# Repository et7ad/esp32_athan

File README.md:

# Athan clock

> **The website: [et7ad.github.io/esp32_athan](https://et7ad.github.io/esp32_athan/).** Try the clock in your browser
> (its screen, joystick and menu), set one up step by step, listen to every athan and radio station, see your mosque's
> times for the whole year, and build your own with the parts list, the wiring and the case in 3D.

A small Wi-Fi clock that calls the athan at your mosque's prayer times. It shows the time and the next prayer,
plays Quran radio, and can switch a relay before Fajr (one controlling a room light, for example). It runs on an
ESP32-S3 with a small amplifier, and keeps its sounds and a whole year of prayer times in its own memory, so the
athan keeps playing without internet.

> **Have an older clock (ESP8266 with a DFPlayer, "version 2")?** Its firmware and prayer times are in
> [et7ad/esp_athan](https://github.com/et7ad/esp_athan), which supports the clocks already in use. New clocks use
> this repository.

## Why the prayer times come from this repository

Every mosque publishes its prayer times its own way: a PDF, a web page, a spreadsheet, an app. Rather than teach
the clock all of them, this project splits the job of keeping a clock in step with its mosque into two parts.

The clock's part is small, and the same for every mosque. It downloads its mosque's times for a whole year from
this repository on GitHub, as one small file in one fixed format ([prayertimes_specs.md](prayertimes_specs.md)),
and keeps them in its own memory. It never contacts a mosque's website, so a site that changes or goes offline
can't affect it. The list of mosques it offers comes from here as well, so adding a mosque needs no change to the
clock.

The other part, getting each mosque's times right, happens here before anything reaches a clock. A mosque's
timetable becomes that one file in whatever way suits that mosque: a script that reads its PDF or web page, a table
the mosque sends in, or a check against its own source when a time looks wrong. The scripts check every file before
it is published ([guides/maintaining.md](guides/maintaining.md)). Clocks download each new year by themselves; a
correction to the current year reaches a clock when Refresh Prayer Times is pressed on its web page.

That is the main idea of the project: the clock stays simple and keeps working, and all the work of following each
mosque happens in one place, with whatever tools it takes.

## Setting up your clock

> **Wi-Fi: 2.4 GHz only.** The clock can't join a 5 GHz network. If your router shows two networks (for example
> "home" and "home-5G"), pick the one without "5G". A router that uses one name for both bands works too.

1. Plug the clock into a USB-C charger (5 V, 2 A).
2. Connect it to your Wi-Fi. A new clock offers two ways at once; use whichever suits your phone.
   - Option1: Over Bluetooth (easiest), from an Android phone or a computer: open <https://www.improv-wifi.com> in Chrome or Edge (safari won't work as it doesn't support Web Bluetooth). Under "Improv via BLE", the page shows a **Connect** button;
     press **Connect** and pick **athan**. When the clock's screen says **BT: press Select**, push the joystick in.
     Then type your network SSID (which is the name of your Wi-Fi network) and type its password.
   - Option2: With any phone, iPhones included, or a computer: join the Wi-Fi network `AthanFallbackHotspot` with the password `athan404`.
      A setup page opens (if it doesn't, open <http://192.168.4.1>). Pick your network, type its password and save.
3. Choose your mosque. A new clock starts with the Islamic Center of Davis: pick yours by name under **Location**, on the clock's web page (below) or in its menu. The clock then downloads the year's prayer times and its sounds, which takes a few minutes the first time.

From then on the clock runs by itself and keeps its Wi-Fi and settings through power cuts. For the athan it needs
the internet only to set its time after a power cut. If your mosque isn't in the list, open an
[issue](https://github.com/et7ad/esp32_athan/issues) with its timetable. Once it is added here, it shows up on every
clock by itself.

## Using it

### The joystick

The clock has one 5-way joystick: Up, Down, Left, Right, and Select (push it straight in).

| Key | On the clock screen |
|---|---|
| Select | Opens the menu |
| Up | Radio on or off |
| Down | Relay on or off |
| Left, Right | Volume down or up |

While the athan or another sound plays, Up, Down and Select stop it.

In the menu, Up and Down move between rows, Left and Right change the choice, and Select takes it. The last row,
Exit, returns to the clock, and so does a minute without a press.

### The web page

On a phone or computer on the same Wi-Fi, open <http://athan.local>. If it doesn't open (some phones, Android in
particular, can't open `.local` addresses), use the clock's IP address instead: it is on the menu's **Info** row.

The page has everything the menu has, in groups: what plays now, the volumes, the athan on or off for each prayer,
the hourly tick and its hours, the Pre-Fajr Tawashih, the radio and its ten stations, your mosque, the screen, and
updates. A change takes effect at once, and the page always shows what the clock is doing, also after a change
made with the joystick.

The sounds have a page of their own, <http://athan.local/audio> (the **Change Sounds At** link on the main page).
For the athan, the Fajr athan, the tawashih and the hourly tick, choose one from the project's list, listen to a
preview and download it, or upload an MP3 of your own.

### Updates

The clock looks for new firmware when it starts and once a day, and it never installs an update by itself. When a
new version is out, a small up arrow appears at the top right of the screen and stays there until you install it:

Install it with **Firmware** on the web page or the menu's **Update** row, at a time when no prayer is due in the
next few minutes: the clock stands still while it downloads, then restarts with the new version. Your settings,
sounds and prayer times stay.

### Good to know

- When children can reach the clock, lock its buttons with the menu's **Lock Buttons** row. To unlock, switch off
  **Buttons Locked** on the web page, or plug the clock in while holding Up, Down, Left or Right.
- To move the clock to another Wi-Fi network, unplug it, hold Select, and plug it back in. It forgets its network
  and setup starts again.
- Home Assistant finds the clock through its ESPHome integration, with the same controls as the web page. The
  encryption key it asks for is in [guides/using.md](guides/using.md#4-the-web-page) section 4.

The full guide is [guides/using.md](guides/using.md): the screen and its marks, every menu row, your own sounds and
radio stations, and what to do if your router keeps dropping the clock.

## What it does

- Calls the athan at Dhuhr, Asr, Maghrib and Isha, and a separate Fajr athan at Fajr, each at its own volume. Each
  prayer's athan can be switched off on its own.
- Downloads a whole year of your mosque's prayer times from this repository and keeps it. Once the clock is set,
  the athan needs no internet.
- Plays Quran radio from ten slots. They follow this project's station list, and any slot can play a link of your
  own instead.
- Pre-Fajr Tawashih (off by default): 25 minutes before Fajr it switches the relay on and plays a tawashih, then
  switches the relay off 15 minutes after it ends.
- Plays an hourly tick during the hours you choose.
- Lets you choose each sound (athan, Fajr athan, tawashih, tick) from the project's list, or upload your own.
- Is set up from a phone, over Bluetooth or through its own Wi-Fi hotspot.
- Has a web page, works with Home Assistant, and updates its own firmware.
- Comes with a one-colour OLED or a colour screen, and keeps calling the athan even if the screen fails.

## Guides

| You want to | Read |
|---|---|
| Set up a clock and use it | [guides/using.md](guides/using.md) |
| Build one | [guides/building.md](guides/building.md) |
| Keep the prayer times, sounds and stations up to date, or publish firmware | [guides/maintaining.md](guides/maintaining.md) |
| Understand or change the firmware | [DEVELOPER.md](DEVELOPER.md), and [firmware_rules.md](firmware_rules.md) for the rules it depends on |
| Understand the circuit board | [HARDWARE.md](HARDWARE.md), [max98357a_amplifier.md](max98357a_amplifier.md), [microcontroller_demand.md](microcontroller_demand.md) |
| Read or write a prayer-time file | [prayertimes_specs.md](prayertimes_specs.md) |

**Status:** firmware 3.0.0 runs on the breadboard prototype. The circuit board (`hardware/pcb/`) and its
3D-printed case (`hardware/enclosure/`) are designed.

## Repository layout

```text
firmware/
  athan.yaml               everything the clock does (ESPHome)
  displays/                one file per display (oled.yaml, tft.yaml); athan.yaml uses one of them
  partitions.csv           the 16 MB flash layout (two app slots, prayer years, sounds)
  web_audio_link.js        makes the web page's Change Sounds At value a link
  components/athan/        the custom component: stored sounds, lists, radio, prayer years, the sounds page
  sounds/                  click.wav and volume.wav, the two menu tones
  tests/                   tests and checks that run on a computer
docs/                      everything the clocks download, and the website (GitHub Pages)
  athantimes/              mosques.json (the mosques) and a folder per mosque, a file per year
  audio/                   catalog.json and the sounds (athan/ fajr/ tawashih/ tick/)
  radio/stations.json      the project's ten radio stations
  *.html, assets/          the website's pages, scripts, pictures and 3D models
guides/                    using.md, building.md, maintaining.md
scripts/                   prayer-time converters, the sound library builder, the release manifest
hardware/pcb/              the KiCad project
hardware/enclosure/        the 3D-printed case (STL to print, STEP, the CadQuery script)
hardware/programmer/       a press-in programmer for J6 (KiCad project)
images/                    pictures for the guides
build_firmware.sh          build, flash and update without Docker (guides/building.md)
flash_firmware.sh          flash existing files over Wi-Fi or USB, without building
README.md  HARDWARE.md  DEVELOPER.md  firmware_rules.md  prayertimes_specs.md
max98357a_amplifier.md  microcontroller_demand.md
```

## License

See [LICENSE](LICENSE).

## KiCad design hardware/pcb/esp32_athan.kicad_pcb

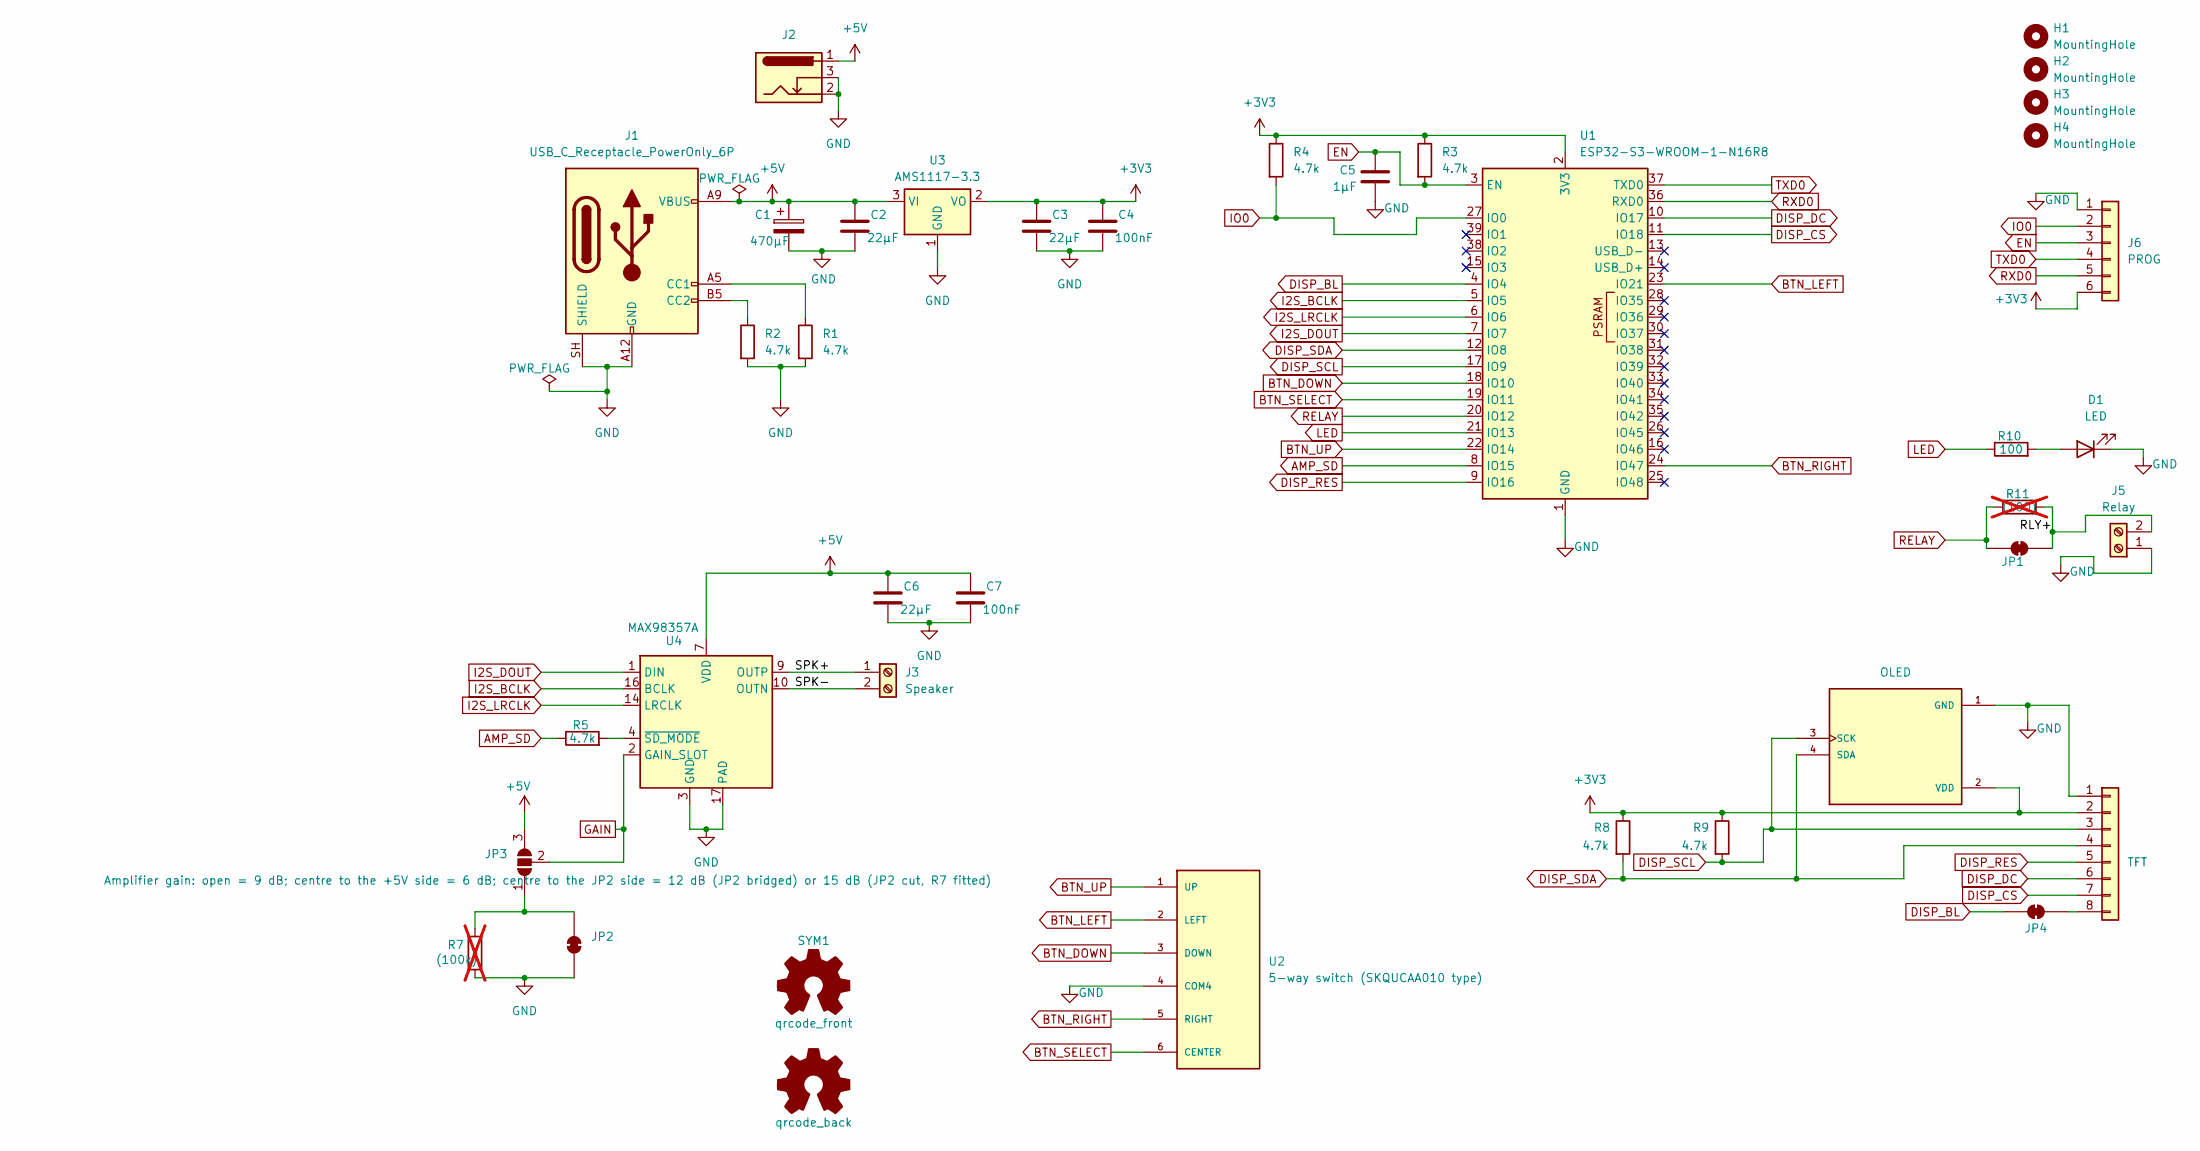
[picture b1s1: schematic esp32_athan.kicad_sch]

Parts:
C1: 470µF; CP_Elec_8x10.5; LCSC C178530
C2, C3, C6: 22µF; C_1206_3216Metric; LCSC C12891
C4, C7: 100nF; C_1206_3216Metric; LCSC C24497
C5: 1µF; C_1206_3216Metric; LCSC C1848
D1: LED; LED_1206_3216Metric_Pad1.42x1.75mm_HandSolder; LCSC C130717
DS1: OLED; LCD_OLED_128X64_1.3_I2C; PARTREV NA
DS2: TFT; Display_TFT_1.54in_ST7789_240x240_8pin
H1, H2, H3, H4: MountingHole; MountingHole_3.2mm_M3
J1: USB_C_Receptacle_PowerOnly_6P; USB_C_Receptacle_GCT_USB4125_6P_BothSides; LCSC C3151650
J2: Barrel_Jack; BarrelJack_CUI_PJ-102AH_Horizontal; LCSC C3096093
J3: Speaker; TerminalBlock_MaiXu_MX126-5.0-02P_1x02_P5.00mm; LCSC C5188434
J5: Relay; TerminalBlock_MaiXu_MX126-5.0-02P_1x02_P5.00mm; LCSC C5188434
J6: PROG; PinHeader_1x06_P2.54mm_Vertical
JP1, JP2, JP4: SolderJumper_2_Bridged; SolderJumper-2_P1.3mm_Bridged_RoundedPad1.0x1.5mm
JP3: SolderJumper_3_Open; SolderJumper-3_P1.3mm_Open_RoundedPad1.0x1.5mm
R1, R2, R3, R4, R5, R8, R9: 4.7k; R_1206_3216Metric; LCSC C17936
R7: (100k); R_1206_3216Metric; LCSC C17900; not fitted
R10: 100; R_1206_3216Metric; LCSC C17901
R11: (100); R_1206_3216Metric; LCSC C17901; not fitted
SYM1: qrcode_front; QRCode_esp32_athan_p3
SYM2: qrcode_back; QRCode_esp32_athan_p3
U1: ESP32-S3-WROOM-1-N16R8; ESP32-S3-WROOM-1; LCSC C2913202
U2: 5-way switch (SKQUCAA010 type); SKQUAAA010
U3: AMS1117-3.3; SOT-223-3_TabPin2; LCSC C6186
U4: MAX98357A; TQFN-16-1EP_3x3mm_P0.5mm_EP1.23x1.23mm; LCSC C910544

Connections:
+3V3: C3.1, C4.1, DS1.2 (VDD), DS2.2, J6.6, R3.1, R4.1, R8.1, R9.1, U1.2 (3V3), U3.2 (VO)
+5V: C1.1, C2.1, C6.1, C7.1, J1.A9 (VBUS), J1.B9 (VBUS), J2.1, JP3.3 (B), U3.3 (VI), U4.7 (VDD), U4.8 (VDD)
/RLY+: J5.2, JP1.2 (B), R11.2
/SPK+: J3.1, U4.9 (OUTP)
/SPK-: J3.2, U4.10 (OUTN)
AMP_SD: R5.1, U1.8 (IO15)
BTN_DOWN: U1.18 (IO10), U2.3 (DOWN)
BTN_LEFT: U1.23 (IO21), U2.2 (LEFT)
BTN_RIGHT: U1.24 (IO47), U2.5 (RIGHT)
BTN_SELECT: U1.19 (IO11), U2.6 (CENTER)
BTN_UP: U1.22 (IO14), U2.1 (UP)
DISP_BL: JP4.1 (A), U1.4 (IO4)
DISP_CS: DS2.7, U1.11 (IO18)
DISP_DC: DS2.6, U1.10 (IO17)
DISP_RES: DS2.5, U1.9 (IO16)
DISP_SCL: DS1.3 (SCK), DS2.3, R9.2, U1.17 (IO9)
DISP_SDA: DS1.4 (SDA), DS2.4, R8.2, U1.12 (IO8)
EN: C5.1, J6.3, R3.2, U1.3 (EN)
GAIN: JP3.2 (C), U4.2 (GAIN_SLOT)
GND: C1.2, C2.2, C3.2, C4.2, C5.2, C6.2, C7.2, D1.1 (K), DS1.1 (GND), DS2.1, J1.A12 (GND), J1.B12 (GND), J1.SH (SHIELD), J2.2, J2.3, J5.1, J6.1, JP2.1 (A), R1.2, R2.2, R7.2, U1.1 (GND), U1.40 (GND), U1.41 (GND), U2.4 (COM4), U3.1 (GND), U4.3 (GND), U4.11 (GND), U4.15 (GND), U4.17 (PAD)
I2S_BCLK: U1.5 (IO5), U4.16 (BCLK)
I2S_DOUT: U1.7 (IO7), U4.1 (DIN)
I2S_LRCLK: U1.6 (IO6), U4.14 (LRCLK)
IO0: J6.2, R4.2, U1.27 (IO0)
LED: R10.1, U1.21 (IO13)
unnamed: D1.2 (A), R10.2
unnamed: DS2.8, JP4.2 (B)
unnamed: J1.A5 (CC1), R1.1
unnamed: J1.B5 (CC2), R2.1
unnamed: JP2.2 (B), JP3.1 (A), R7.1
unnamed: R5.2, U4.4 (~SD_MODE)
RELAY: JP1.1 (A), R11.1, U1.20 (IO12)
RXD0: J6.5, U1.36 (RXD0)
TXD0: J6.4, U1.37 (TXD0)

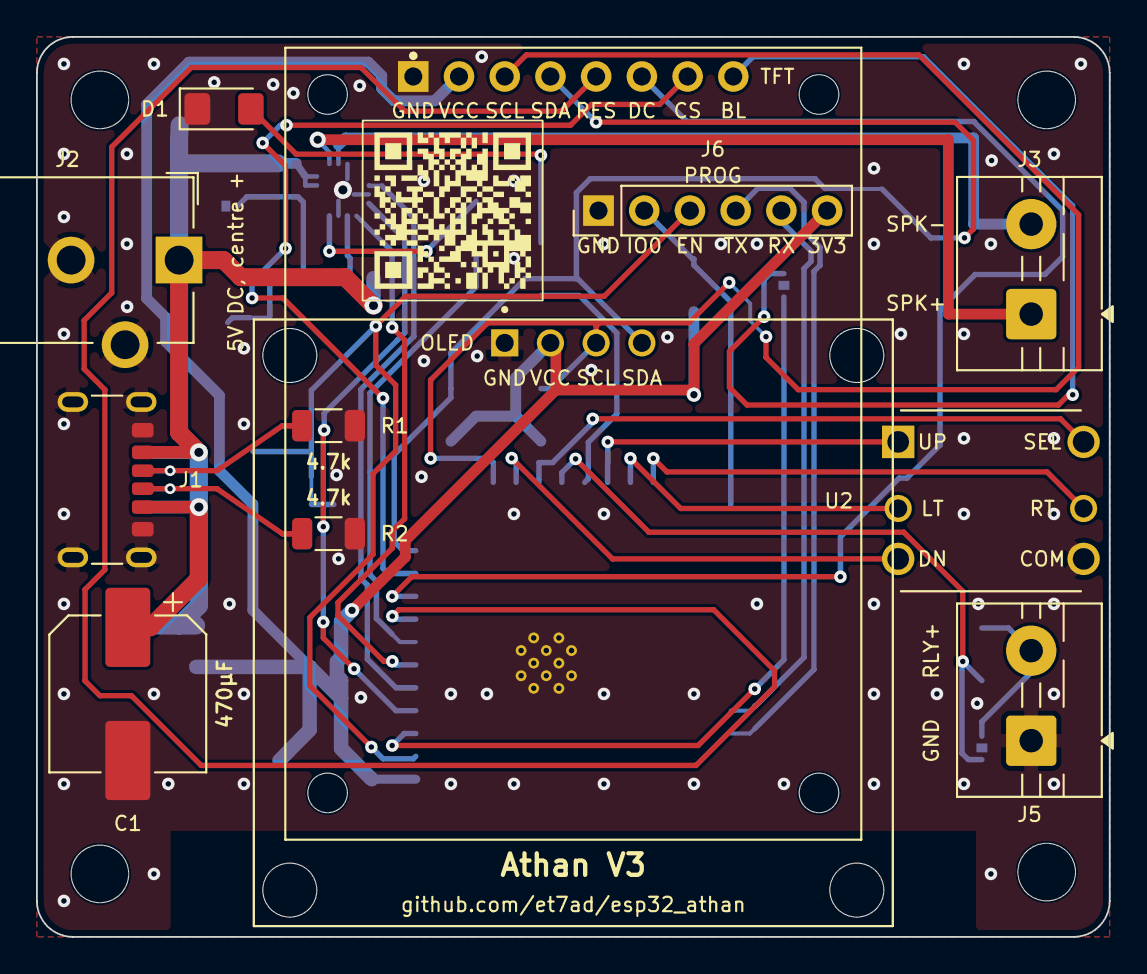
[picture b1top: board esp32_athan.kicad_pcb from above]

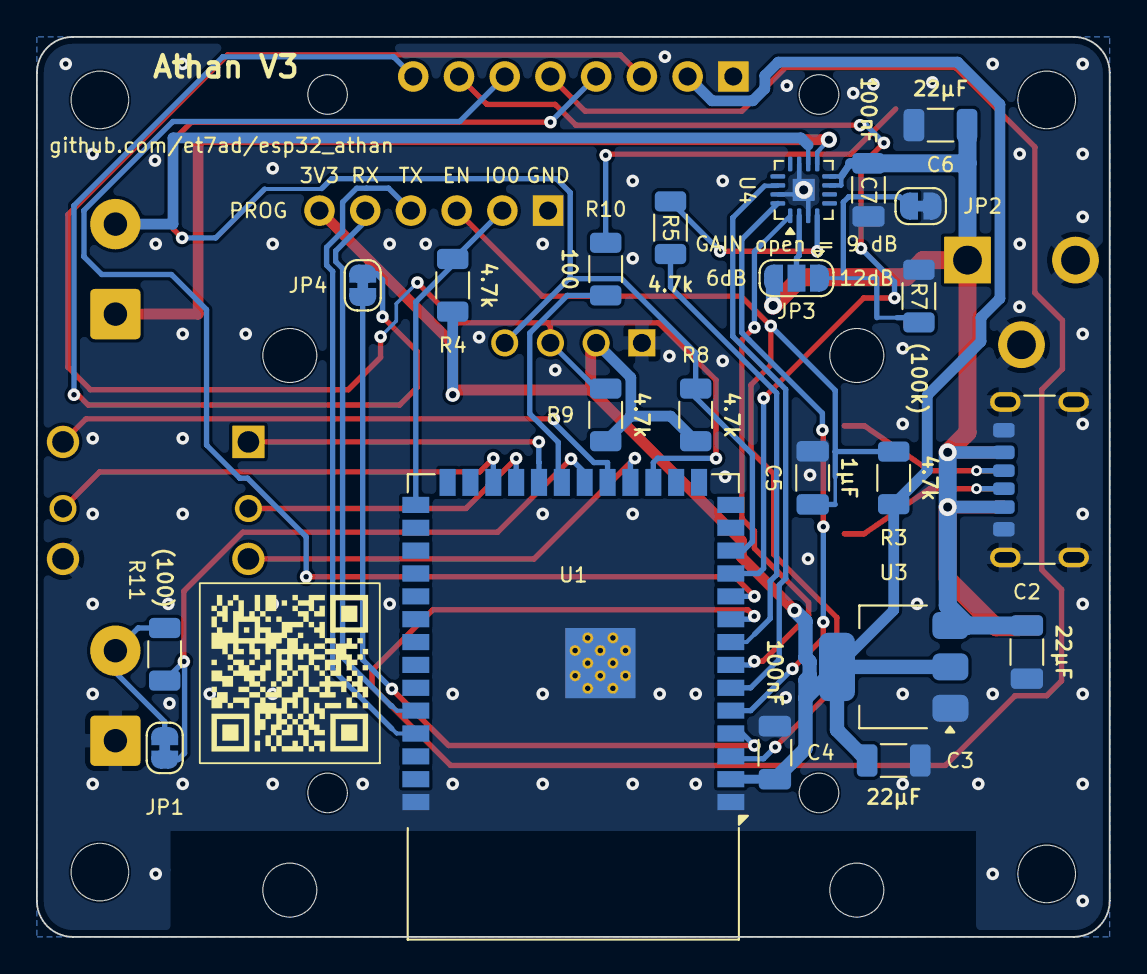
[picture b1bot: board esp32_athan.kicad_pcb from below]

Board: 2 copper layers, 59.6 x 50.0 mm, 39 parts (22 on the bottom side), 34 nets.

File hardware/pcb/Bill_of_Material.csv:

"Reference","Qty","Value","Footprint","Datasheet","Description"
"C1","1","470µF","Capacitor_SMD:CP_Elec_8x10.5","","Bulk capacitor on +5V for the amplifier’s peaks: 470 µF 10 V low-ESR electrolytic, 8 mm"
"C2,C3,C6","3","22µF","Capacitor_SMD:C_1206_3216Metric","","Amplifier supply capacitor on +5V, at U4: 22 µF ceramic, 10 V or more,Regulator input capacitor on +5V (U3): 22 µF ceramic, 10 V or more,Regulator output capacitor on +3V3 (U3), near the module’s 3V3 pin: 22 µF ceramic"
"C4,C7","2","100nF","Capacitor_SMD:C_1206_3216Metric","","+3V3 decoupling at the module’s 3V3 pin: 100 nF ceramic,Amplifier VDD decoupling, right at U4’s VDD pins: 100 nF ceramic"
"C5","1","1µF","Capacitor_SMD:C_1206_3216Metric","","EN power-on delay with R3 (holds the module in reset while +3V3 rises): 1 µF ceramic"
"D1","1","LED","LED_SMD:LED_1206_3216Metric_Pad1.42x1.75mm_HandSolder","","Status LED, blue, 1206 (GPIO13 through R10)"
"DS1","1","OLED","Library:LCD_OLED_128X64_1.3_I2C","","Display header for a 1.3-inch SH1106 (or 0.96-inch SSD1306) 128x64 I2C OLED module: GND, VCC, SCL, SDA"
"DS2","1","TFT","Library:Display_TFT_1.54in_ST7789_240x240_8pin","","Display header for a 1.54-inch ST7789 240x240 SPI TFT module: GND, VCC, SCL, SDA, RES, DC, CS, BL [https://oshwlab.com/scrators/st7789] [https://www.amazon.com/dp/B0DN9NMBFW?ref=ppx_yo2ov_dt_b_fed_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"
"J1","1","USB_C_Receptacle_PowerOnly_6P","Library:USB_C_Receptacle_GCT_USB4125_6P_BothSides","https://www.usb.org/sites/default/files/documents/usb_type-c.zip","USB-C power input, 5 V (power only, no data); fits on the front or the back"
"J2","1","Barrel_Jack","Connector_BarrelJack:BarrelJack_CUI_PJ-102AH_Horizontal","","5 V DC barrel jack, centre positive (CUI PJ-102AH); regulated 5 V only"
"J3","1","Speaker","TerminalBlock:TerminalBlock_MaiXu_MX126-5.0-02P_1x02_P5.00mm","","Speaker terminal: a 4 Ω, 3 W speaker (pin 1 SPK+, pin 2 SPK−)"
"J5","1","Relay","TerminalBlock:TerminalBlock_MaiXu_MX126-5.0-02P_1x02_P5.00mm","","Relay output: pin 2 is a 3.3 V logic signal for a relay module (GPIO12 through JP1), pin 1 GND"
"J6","1","PROG","Connector_PinHeader_2.54mm:PinHeader_1x06_P2.54mm_Vertical","","Programming header: GND, IO0, EN, TX, RX, 3V3 (a jumper on pins 1 and 2 at power-up starts download mode)"
"R1,R2,R3,R4,R5,R8,R9","7","4.7k","Resistor_SMD:R_1206_3216Metric","","Amplifier SD_MODE from GPIO15 (4.7 to 10 kΩ): high plays the left channel,DISP_SCL pull-up to +3V3, for the OLED's I2C clock (with a TFT the line carries the SPI clock),DISP_SDA pull-up to +3V3, for the OLED's I2C data (with a TFT the line carries SPI data),EN pull-up to +3V3 (4.7 to 10 kΩ); with C5 the power-on delay,GPIO0 pull-up to +3V3 (4.7 to 10 kΩ): high at reset is a normal boot,USB-C CC1 pull-down to GND: USB-C asks for 5.1 kΩ ±20 %, so 4.08 to 6.12 kΩ,USB-C CC2 pull-down to GND: USB-C asks for 5.1 kΩ ±20 %, so 4.08 to 6.12 kΩ"
"R7","1","(100k)","Resistor_SMD:R_1206_3216Metric","","Optional, for 15 dB gain: fit it and cut JP2, with JP3’s centre bridged to the JP2 side"
"R10","1","100","Resistor_SMD:R_1206_3216Metric","","Status LED resistor, 100 to 330 Ω: 100 Ω for blue, green and white LEDs (about 2.7 to 3 V), 300 to 330 Ω for red, orange and yellow (about 2 V)"
"R11","1","(100)","Resistor_SMD:R_1206_3216Metric","","Optional series resistor on the relay output (about 100 Ω): fit it and cut JP1"
"U1","1","ESP32-S3-WROOM-1-N16R8","RF_Module:ESP32-S3-WROOM-1","https://www.espressif.com/sites/default/files/documentation/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","RF Module, ESP32-S3 SoC, Wi-Fi 802.11b/g/n, Bluetooth, BLE, 32-bit, 3.3V, onboard antenna, SMD"
"U2","1","5-way switch (SKQUCAA010 type)","SKQUAAA010:SKQUAAA010","","5-way switch, 10 x 10 mm through-hole, 4 directions and a centre push: Alps SKQUCAA010 or a copy (sold as 5-way switch 10*10*10 mm). Not SKQUAAA010, which has no centre push"
"U3","1","AMS1117-3.3","Package_TO_SOT_SMD:SOT-223-3_TabPin2","http://www.advanced-monolithic.com/pdf/ds1117.pdf","1A Low Dropout regulator, positive, 3.3V fixed output, SOT-223: makes +3V3 from +5V"
"U4","1","MAX98357A","Package_DFN_QFN:TQFN-16-1EP_3x3mm_P0.5mm_EP1.23x1.23mm","https://www.analog.com/media/en/technical-documentation/data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","Mono I2S DAC and class-D amplifier, 3.2 W into 4 Ω, TQFN-16 (3 × 3 mm)"

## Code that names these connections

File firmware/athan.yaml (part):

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  log_level: DEBUG

  # Pins: HARDWARE.md section 3
  pin_i2s_bclk: GPIO5
  pin_i2s_lrclk: GPIO6
  pin_i2s_dout: GPIO7
  pin_amp_sd: GPIO15       # MAX98357A SD_MODE through 4.7 kOhm: high = on (left channel), low/floating = off
  pin_sda: GPIO8           # display: I2C data (OLED) or SPI data (TFT), header pin 4
  pin_scl: GPIO9           # display: I2C clock (OLED) or SPI clock (TFT), header pin 3
  # The 5-way switch: each direction and the centre push switch to GND (internal pull-ups). Any of the five
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  pin_left: GPIO21
  pin_right: GPIO47
  pin_select: GPIO11       # centre push
  pin_relay: GPIO12
  pin_led: GPIO13

  # Volume curve: 10 % plays this many dB below full, rising evenly to 100 % = full (0 % = silent).
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# ---------------------------------------------------------------------------------------------------------------------
i2s_audio:
  - id: i2s_out
    i2s_lrclk_pin: ${pin_i2s_lrclk}
    i2s_bclk_pin: ${pin_i2s_bclk}

speaker:
  - platform: i2s_audio
    id: i2s_speaker
    i2s_audio_id: i2s_out
    i2s_dout_pin: ${pin_i2s_dout}
    dac_type: external
    sample_rate: 44100
    bits_per_sample: 16bit
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output:
  - platform: gpio
    id: amp_enable
    pin: ${pin_amp_sd}
  - platform: gpio
    id: led_output
    pin: ${pin_led}
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  - platform: gpio
    id: external_relay
    name: "External Relay"
    pin: ${pin_relay}
    restore_mode: RESTORE_DEFAULT_OFF
    web_server:
      sorting_group_id: grp_system
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          id(radio_resume) = -1;
          if (r >= 0 && !id(athan_playing)) { id(radio_slot) = r; id(radio_start).execute(); }
          id(prefajr_relay_off).execute(${prefajr_relay_min} * 60000 - 7000);
  # The Pre-Fajr relay's own timer (restart: the last call counts), apart from run_prefajr so that stopping that
  # script never leaves the relay on.
  - id: prefajr_relay_off
    mode: restart
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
